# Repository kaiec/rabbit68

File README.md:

# The Rabbit68 Keyboard

## Layout

http://www.keyboard-layout-editor.com/#/gists/c885816c6b763c657e40474b015e362b

## Design Principles

- Basis for experiments and customization at low cost.
- Ortholinear
- Only keys without stabilizers, i.e., 1.75 U maximum.
- Key sizes that are available in a standard (blank) qwerty keycaps set.
- No SMD

## Piggybacked Teensy 2.0

The PCB uses a Teensy 2.0 as controller. This way the whole PCB is basically just to avoid handwiring.

## Shopping List

This is what I use for the very first prototype. Neither fancy, nor quality, maybe not even good looking. We will see. Especially the switches seem way too cheap... but it should be good enough to test the overall layout and gain experiences with the design and build process.

- PCB: 
  - JLCPCB, about 20€ per 5 PCBs = 4€
- Controller
  - Teensy 2.0, eBay, 10€
- Diodes:
  - 1N4148, 500 pcs 3.38€ at Amazon = 1€
- Caps (ultra cheap standard sets, make sure all required sizes are contained): 
   - Schwarz blank PBT 61 ANSI Keybord Schlüsselkappen Set für MX Switches Mechanische Tastatur, eBay 12.62€
   - 104 Keycaps PBT Backlit Double-Shot für Mechanical Cherry MX Switch 10 Farben, eBay 9.91€
- Switches
  - MX Brown Switches, 10 pcs for 1.59€, eBay, 8 sets (to have some spares): 11.92€
- Case:
  - Some cheap wood, tbd
  - Some screws
  - Magnets (maybe, we'll see)

Sum: ~ 45 - 50 €

## Similar projects

### Shark PCB
- https://github.com/Gondolindrim/SharkPCB
- https://www.reddit.com/r/MechanicalKeyboards/comments/a2s485/sharkpcb_design_stream/

### DIY Low Profile Ortho
- https://easyeda.com/7zark7/Kailh-Ortholinear
- https://imgur.com/a/gqjEYFf
- https://www.reddit.com/r/MechanicalKeyboards/comments/8sy17h/diy_low_profile_ortho/

## Guides
- https://github.com/ruiqimao/keyboard-pcb-guide
- https://kbwiki.ai03.me/books/pcb-design

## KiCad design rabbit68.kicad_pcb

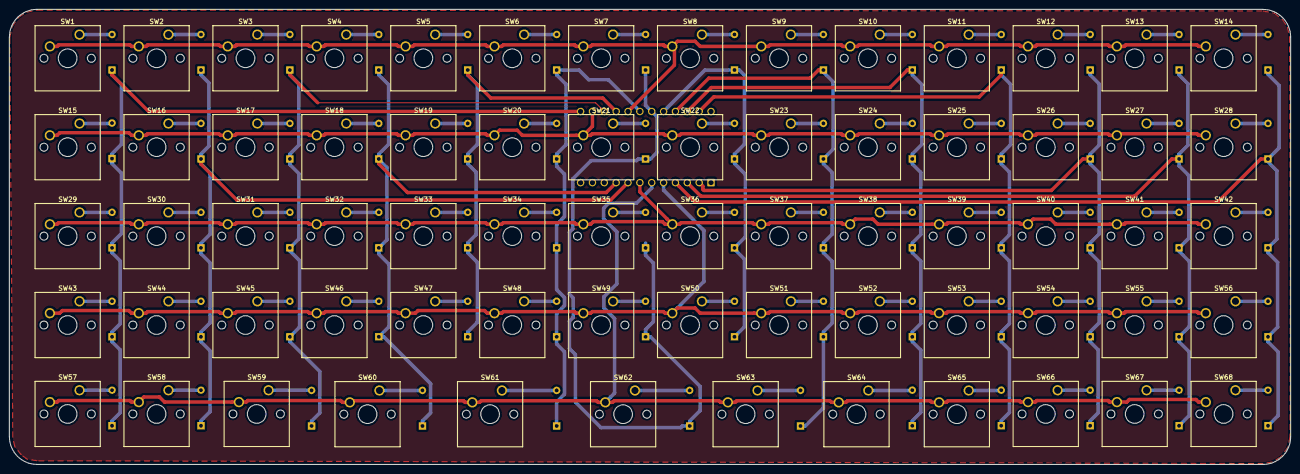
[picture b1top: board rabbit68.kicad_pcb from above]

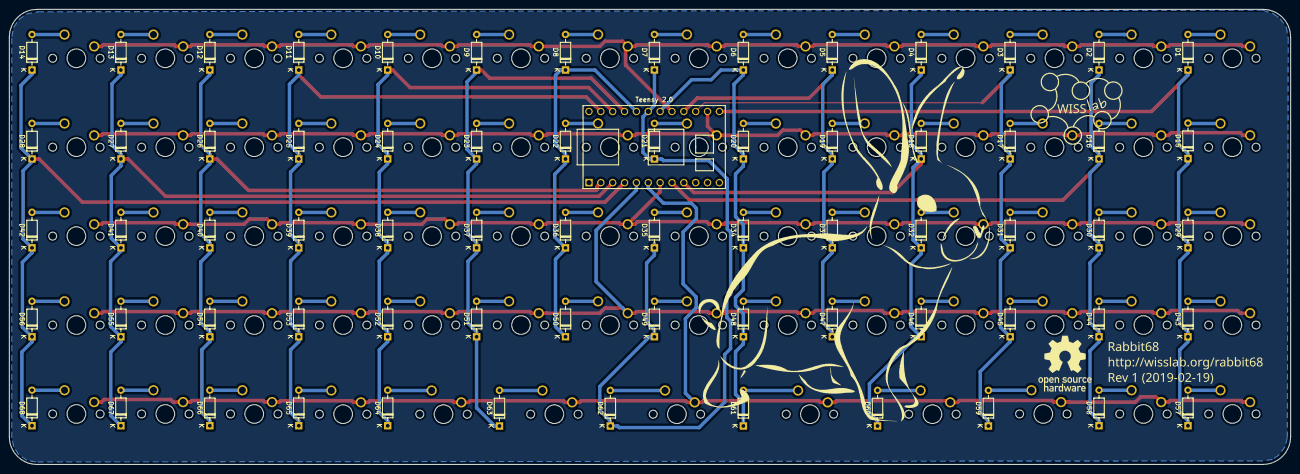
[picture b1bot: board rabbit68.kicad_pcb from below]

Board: 2 copper layers, 274.5 x 97.5 mm, 137 parts (69 on the bottom side), 87 nets.

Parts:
D1, D2, D3, D4, D5, D6, D7, D8, D9, D10, D11, D12, D13, D14, D15, D16, D17, D18, D19, D20, D21, D22, D23, D24, D25, D26, D27, D28, D29, D30, D31, D32, D33, D34, D35, D36, D37, D38, D39, D40, D41, D42, D43, D44, D45, D46, D47, D48, D49, D50, D51, D52, D53, D54, D55, D56, D57, D58, D59, D60, D61, D62, D63, D64, D65, D66, D67, D68: 1N4148; D_DO-35_SOD27_P7.62mm_Horizontal
SW1, SW2, SW3, SW4, SW5, SW6, SW7, SW8, SW9, SW10, SW11, SW12, SW13, SW14, SW15, SW16, SW17, SW18, SW19, SW20, SW21, SW22, SW23, SW24, SW25, SW26, SW27, SW28, SW29, SW30, SW31, SW32, SW33, SW34, SW35, SW36, SW37, SW38, SW39, SW40, SW41, SW42, SW43, SW44, SW45, SW46, SW47, SW48, SW49, SW50, SW51, SW52, SW53, SW54, SW55, SW56, SW57, SW58, SW65, SW66, SW67, SW68: SW_Push; SW_Cherry_MX1A_1.00u_PCB
SW59, SW60, SW63, SW64: SW_Push; SW_Cherry_MX1A_1.25u_PCB
SW61, SW62: SW_Push; SW_Cherry_MX1A_1.50u_PCB
Teensy 2.0: Teensy2.0-Teensy; Teensy2.0

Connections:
/COL1: D1.1, D15.1, D29.1, D43.1, D57.1, Teensy 2.0.18
/COL2: D2.1, D16.1, D30.1, D44.1, D58.1, Teensy 2.0.8
/COL3: D3.1, D17.1, D31.1, D45.1, D59.1, Teensy 2.0.20
/COL4: D4.1, D18.1, D32.1, D46.1, D60.1, Teensy 2.0.9
/COL5: D5.1, D19.1, D33.1, D47.1, Teensy 2.0.21
/COL6: D6.1, D20.1, D34.1, D48.1, D61.1, Teensy 2.0.23
/COL7: D7.1, D21.1, D35.1, D49.1, D62.1, Teensy 2.0.24
/COL8: D8.1, D22.1, D36.1, D50.1, Teensy 2.0.25
/COL9: D9.1, D23.1, D37.1, D51.1, D63.1, Teensy 2.0.26
/COL10: D10.1, D24.1, D38.1, D52.1, D64.1, Teensy 2.0.27
/COL11: D11.1, D25.1, D39.1, D53.1, D65.1, Teensy 2.0.28
/COL12: D12.1, D26.1, D40.1, D54.1, D66.1, Teensy 2.0.2
/COL13: D13.1, D27.1, D41.1, D55.1, D67.1, Teensy 2.0.3
/COL14: D14.1, D28.1, D42.1, D56.1, D68.1, Teensy 2.0.4
/ROW1: SW1.2, SW2.2, SW3.2, SW4.2, SW5.2, SW6.2, SW7.2, SW8.2, SW9.2, SW10.2, SW11.2, SW12.2, SW13.2, SW14.2, Teensy 2.0.22
/ROW2: SW15.2, SW16.2, SW17.2, SW18.2, SW19.2, SW20.2, SW21.2, SW22.2, SW23.2, SW24.2, SW25.2, SW26.2, SW27.2, SW28.2, Teensy 2.0.19
/ROW3: SW29.2, SW30.2, SW31.2, SW32.2, SW33.2, SW34.2, SW35.2, SW36.2, SW37.2, SW38.2, SW39.2, SW40.2, SW41.2, SW42.2, Teensy 2.0.7
/ROW4: SW43.2, SW44.2, SW45.2, SW46.2, SW47.2, SW48.2, SW49.2, SW50.2, SW51.2, SW52.2, SW53.2, SW54.2, SW55.2, SW56.2, Teensy 2.0.5
/ROW5: SW57.2, SW58.2, SW59.2, SW60.2, SW61.2, SW62.2, SW63.2, SW64.2, SW65.2, SW66.2, SW67.2, SW68.2, Teensy 2.0.6
unnamed: D1.2, SW1.1
unnamed: D2.2, SW2.1
unnamed: D3.2, SW3.1
unnamed: D4.2, SW4.1
unnamed: D5.2, SW5.1
unnamed: D6.2, SW6.1
unnamed: D7.2, SW7.1
unnamed: D8.2, SW8.1
unnamed: D9.2, SW9.1
unnamed: D10.2, SW10.1
unnamed: D11.2, SW11.1
unnamed: D12.2, SW12.1
unnamed: D13.2, SW13.1
unnamed: D14.2, SW14.1
unnamed: D15.2, SW15.1
unnamed: D16.2, SW16.1
unnamed: D17.2, SW17.1
unnamed: D18.2, SW18.1
unnamed: D19.2, SW19.1
unnamed: D20.2, SW20.1
unnamed: D21.2, SW21.1
unnamed: D22.2, SW22.1
unnamed: D23.2, SW23.1
unnamed: D24.2, SW24.1
unnamed: D25.2, SW25.1
unnamed: D26.2, SW26.1
unnamed: D27.2, SW27.1
unnamed: D28.2, SW28.1
unnamed: D29.2, SW29.1
unnamed: D30.2, SW30.1
unnamed: D31.2, SW31.1
unnamed: D32.2, SW32.1
unnamed: D33.2, SW33.1
unnamed: D34.2, SW34.1
unnamed: D35.2, SW35.1
unnamed: D36.2, SW36.1
unnamed: D37.2, SW37.1
unnamed: D38.2, SW38.1
unnamed: D39.2, SW39.1
unnamed: D40.2, SW40.1
unnamed: D41.2, SW41.1
unnamed: D42.2, SW42.1
unnamed: D43.2, SW43.1
unnamed: D44.2, SW44.1
unnamed: D45.2, SW45.1
unnamed: D46.2, SW46.1
unnamed: D47.2, SW47.1
unnamed: D48.2, SW48.1
unnamed: D49.2, SW49.1
unnamed: D50.2, SW50.1
unnamed: D51.2, SW51.1
unnamed: D52.2, SW52.1
unnamed: D53.2, SW53.1
unnamed: D54.2, SW54.1
unnamed: D55.2, SW55.1
unnamed: D56.2, SW56.1
unnamed: D57.2, SW57.1
unnamed: D58.2, SW58.1
unnamed: D59.2, SW59.1
unnamed: D60.2, SW60.1
unnamed: D61.2, SW61.1
unnamed: D62.2, SW62.1
unnamed: D63.2, SW63.1
unnamed: D64.2, SW64.1
unnamed: D65.2, SW65.1
unnamed: D66.2, SW66.1
unnamed: D67.2, SW67.1
unnamed: D68.2, SW68.1

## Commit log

2019-02-21 Revision 1, as ordered on 2019-02-20
2019-02-21 Rendered image added
2019-02-21 Cropped
2019-05-29 Case files
2019-09-05 Moved from firmware
2019-09-09 Space filling case parts
